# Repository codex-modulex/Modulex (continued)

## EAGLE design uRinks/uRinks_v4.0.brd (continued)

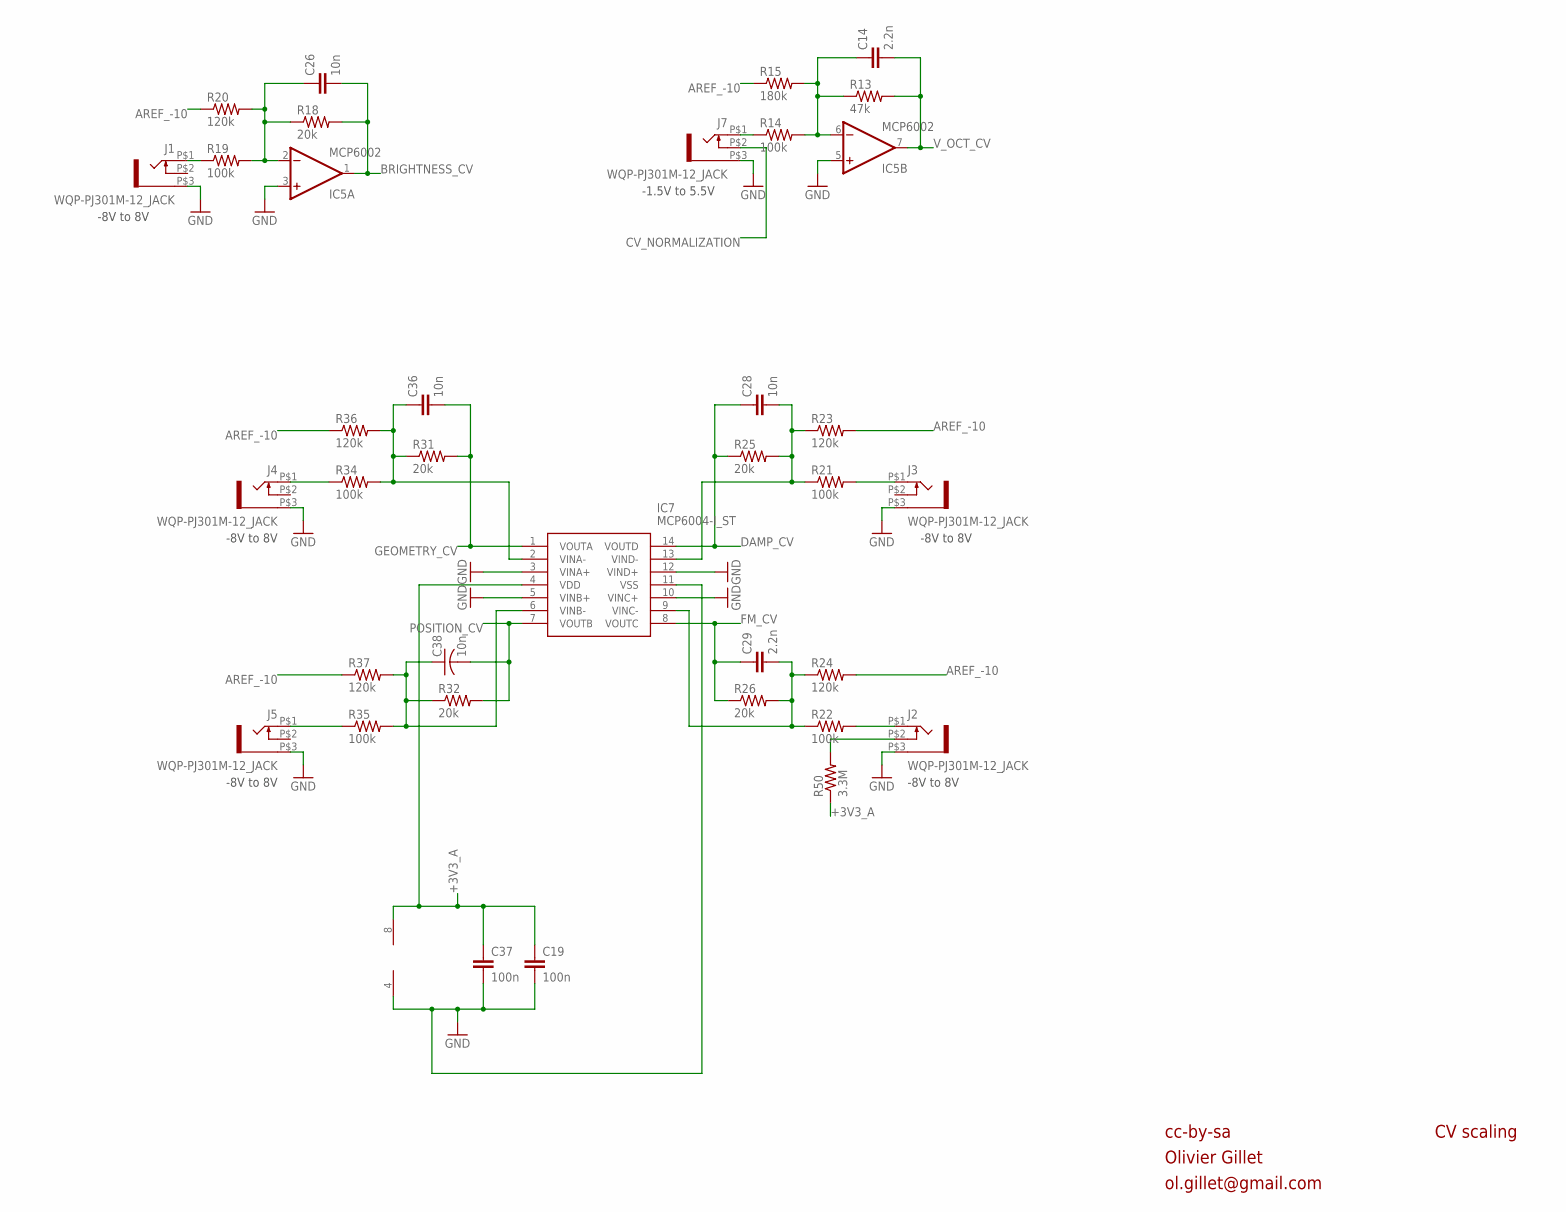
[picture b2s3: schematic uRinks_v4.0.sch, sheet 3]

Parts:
C14, C29: 2.2n; PARTS_AMAN_RESISTOR_0603
C19, C37: 100n; PARTS_AMAN_RESISTOR_0603
C26, C28, C36: 10n; PARTS_AMAN_RESISTOR_0603
C38: 10n; C0603
IC5: MCP6002; SO08
IC7: MCP6004-I_ST; SOP65P640X120-14N
J1, J2, J3, J4, J5, J7: WQP-PJ301M-12_JACK
R13: 47k; PARTS_AMAN_RESISTOR_0603
R14, R19, R21, R22, R34, R35: 100k; PARTS_AMAN_RESISTOR_0603
R15: 180k; PARTS_AMAN_RESISTOR_0603
R18, R25, R26, R31, R32: 20k; PARTS_AMAN_RESISTOR_0603
R20, R23, R24, R36, R37: 120k; PARTS_AMAN_RESISTOR_0603
R50: 3.3M; PARTS_AMAN_RESISTOR_0603

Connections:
+3V3_A: C19.1, C37.1, IC5.8 (V+), IC7.4 (VDD), R50.1; also elsewhere on the board
AREF_-10: R15.1, R20.1, R23.2, R24.2, R36.1, R37.1; also elsewhere on the board
BRIGHTNESS_CV: C26.2, IC5.1 (OUT), R18.2; also elsewhere on the board
CV_NORMALIZATION: J7.P$2 (3); also elsewhere on the board
DAMP_CV: C28.1, IC7.14 (VOUTD), R25.1; also elsewhere on the board
FM_CV: C29.1, IC7.8 (VOUTC), R26.1; also elsewhere on the board
GEOMETRY_CV: C36.2, IC7.1 (VOUTA), R31.2; also elsewhere on the board
GND: C19.2, C37.2, IC5.3 (+IN), IC5.4 (V-), IC5.5 (+IN), IC7.3 (VINA+), IC7.5 (VINB+), IC7.10 (VINC+), IC7.11 (VSS), IC7.12 (VIND+), J1.P$3 (1), J2.P$3 (1), J3.P$3 (1), J4.P$3 (1), J5.P$3 (1), J7.P$3 (1); also elsewhere on the board
unnamed: J1.P$1 (2), R19.1
unnamed: C26.1, IC5.2 (-IN), R18.1, R19.2, R20.2
unnamed: J7.P$1 (2), R14.1
unnamed: J3.P$1 (2), R21.2
unnamed: J2.P$1 (2), R22.2
unnamed: C29.2, IC7.9 (VINC-), R22.1, R24.1, R26.2
unnamed: C14.1, IC5.6 (-IN), R13.1, R14.2, R15.2
unnamed: C28.2, IC7.13 (VIND-), R21.1, R23.1, R25.2
unnamed: J4.P$1 (2), R34.1
unnamed: C36.1, IC7.2 (VINA-), R31.1, R34.2, R36.2
unnamed: J5.P$1 (2), R35.1
unnamed: C38.1, IC7.6 (VINB-), R32.1, R35.2, R37.2
unnamed: J2.P$2 (3), R50.2
POSITION_CV: C38.2, IC7.7 (VOUTB), R32.2; also elsewhere on the board
V_OCT_CV: C14.2, IC5.7 (OUT), R13.2; also elsewhere on the board

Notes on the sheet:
cc-by-sa
Olivier Gillet
ol.gillet@gmail.com
CV scaling
-8V to 8V
-1.5V to 5.5V

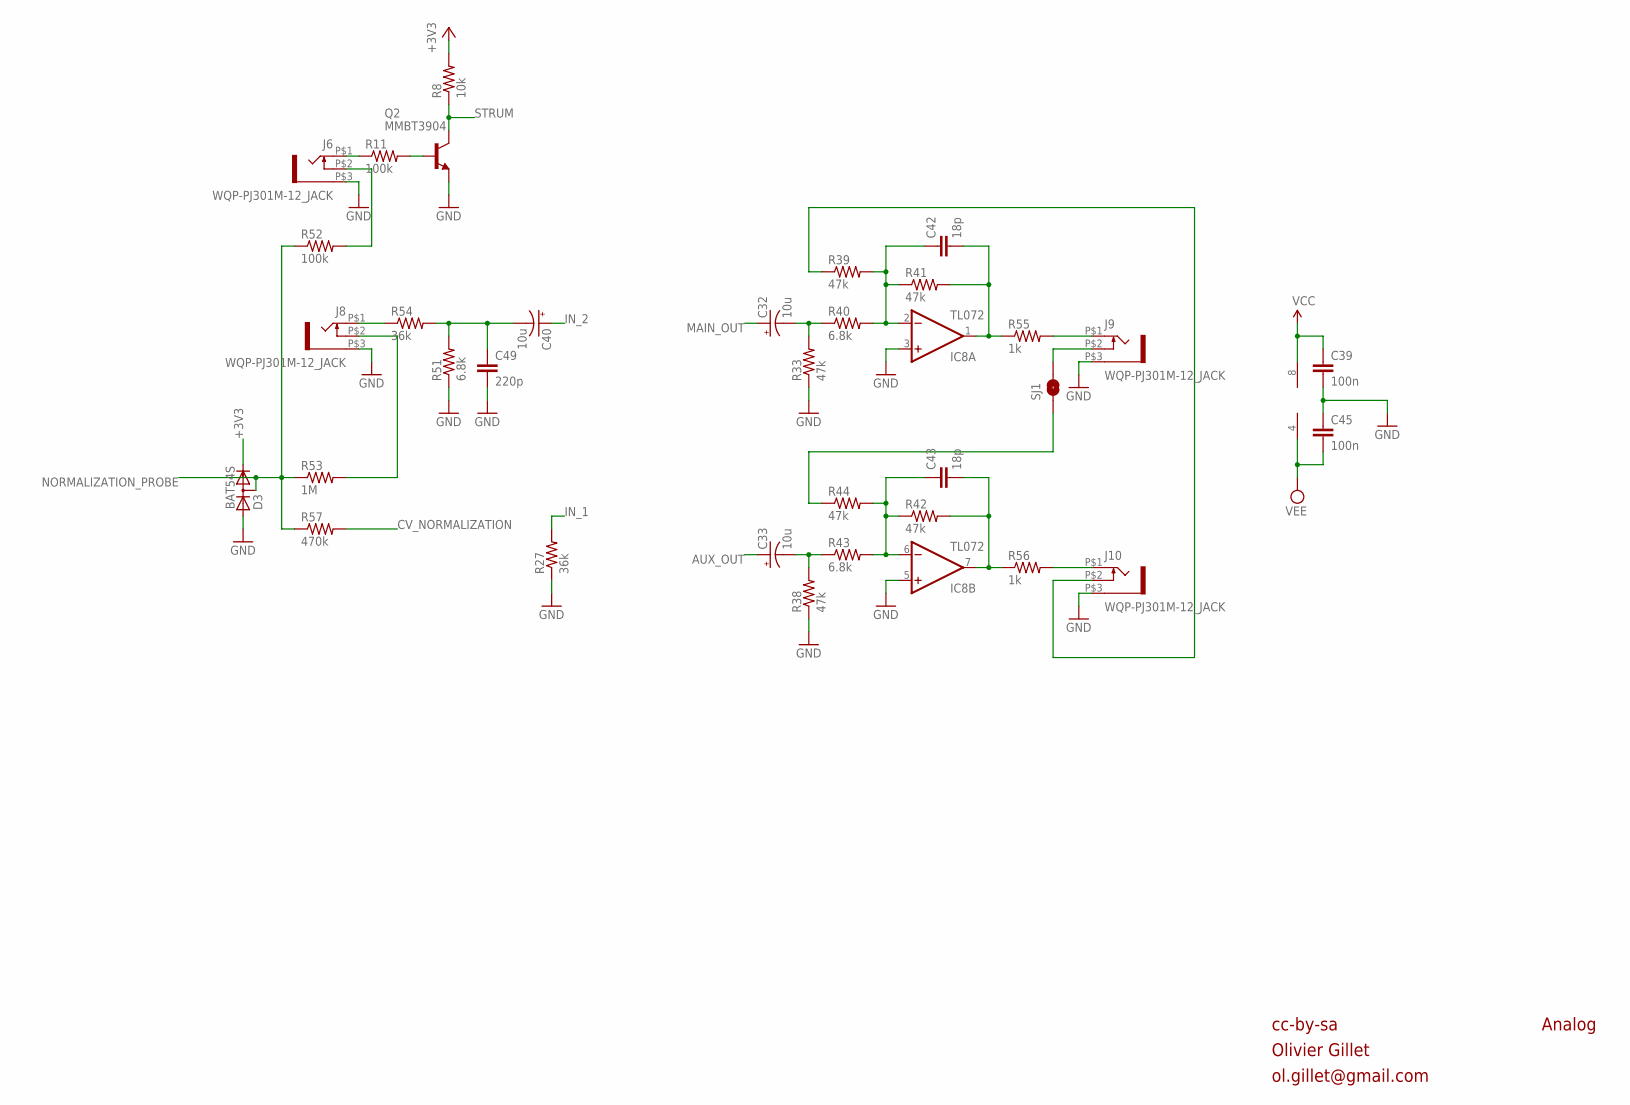
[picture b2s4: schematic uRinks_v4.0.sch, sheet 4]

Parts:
C32, C33, C40: 10u; PANASONIC_A
C39, C45: 100n; PARTS_AMAN_RESISTOR_0603
C42, C43: 18p; PARTS_AMAN_RESISTOR_0603
C49: 220p; PARTS_AMAN_RESISTOR_0603
D3: BAT54S; SOT23
IC8: TL072; SO08
J6, J8, J9, J10: WQP-PJ301M-12_JACK
Q2: MMBT3904; SOT23-BEC
R8: 10k; PARTS_AMAN_RESISTOR_0603
R11: 100k; PARTS_AMAN_RESISTOR_0603
R27, R54: 36k; PARTS_AMAN_RESISTOR_0603
R33, R38, R39, R41, R42, R44: 47k; PARTS_AMAN_RESISTOR_0603
R40, R43, R51: 6.8k; PARTS_AMAN_RESISTOR_0603
R52: 100k; R0603
R53: 1M; PARTS_AMAN_RESISTOR_0603
R55, R56: 1k; PARTS_AMAN_RESISTOR_0603
R57: 470k; PARTS_AMAN_RESISTOR_0603
SJ1: SOLDERJUMPERNC2; SJ_2S-NOTRACE

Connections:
+3V3: D3.2 (C), R8.2; also elsewhere on the board
AUX_OUT: C33.+; also elsewhere on the board
CV_NORMALIZATION: R57.2; also elsewhere on the board
GND: C39.2, C45.1, C49.2, D3.1 (A), IC8.3 (+IN), IC8.5 (+IN), J6.P$3 (1), J8.P$3 (1), J9.P$3 (1), J10.P$3 (1), Q2.E, R27.1, R33.1, R38.1, R51.1; also elsewhere on the board
IN_1: R27.2; also elsewhere on the board
IN_2: C40.+; also elsewhere on the board
MAIN_OUT: C32.+; also elsewhere on the board
unnamed: J6.P$1 (2), R11.1
unnamed: C40.-, C49.1, R51.2, R54.2
unnamed: J6.P$2 (3), R52.2
unnamed: J8.P$1 (2), R54.1
unnamed: C33.-, R38.2, R43.1
unnamed: C43.1, IC8.6 (-IN), R42.1, R43.2, R44.2
unnamed: C43.2, IC8.7 (OUT), R42.2, R56.1
unnamed: J10.P$1 (2), R56.2
unnamed: C32.-, R33.2, R40.1
unnamed: C42.1, IC8.2 (-IN), R39.2, R40.2, R41.1
unnamed: C42.2, IC8.1 (OUT), R41.2, R55.1
unnamed: J9.P$1 (2), R55.2
unnamed: J8.P$2 (3), R53.2
unnamed: J10.P$2 (3), R39.1
unnamed: R44.1, SJ1.1
unnamed: J9.P$2 (3), SJ1.2
unnamed: Q2.B, R11.2
NORMALIZATION_PROBE: D3.3 (AC), R52.1, R53.1, R57.1; also elsewhere on the board
STRUM: Q2.C, R8.1; also elsewhere on the board
VCC: C39.1, IC8.8 (V+); also elsewhere on the board
VEE: C45.2, IC8.4 (V-); also elsewhere on the board

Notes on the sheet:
cc-by-sa
Olivier Gillet
ol.gillet@gmail.com
Analog

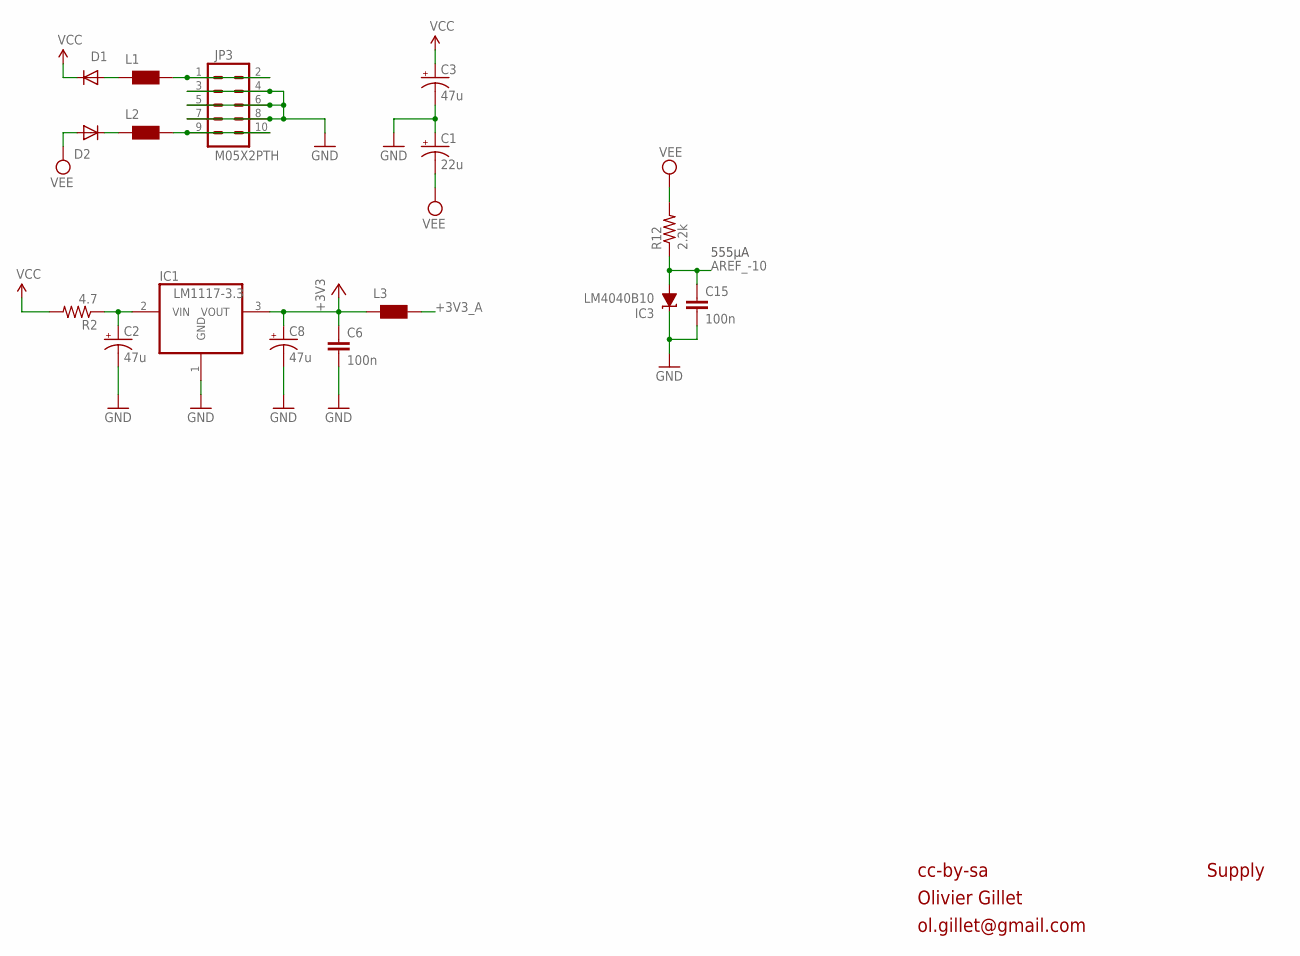
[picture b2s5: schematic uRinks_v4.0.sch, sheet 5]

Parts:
C1: 22u; PANASONIC_C
C2, C3, C8: 47u; PANASONIC_D
C6, C15: 100n; PARTS_AMAN_RESISTOR_0603
D1, D2: 1N5819HW; SOD123
IC1: LM1117-3.3; TO252
IC3: LM4040B10; DBZ_R-PDSO-G3
JP3: M05X2PTH; AVR_ICSP
L1, L2, L3: WE-CBF_0603; 0603
R2: 4.7; R1206
R12: 2.2k; PARTS_AMAN_RESISTOR_0603

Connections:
+3V3: C6.1, C8.+, IC1.3 (VOUT), L3.1; also elsewhere on the board
+3V3_A: L3.2; also elsewhere on the board
AREF_-10: C15.1, IC3.2 (A), R12.1; also elsewhere on the board
GND: C1.+, C2.-, C3.-, C6.2, C8.-, C15.2, IC1.1 (GND), IC3.1 (C), JP3.3, JP3.4, JP3.5, JP3.6, JP3.7, JP3.8; also elsewhere on the board
unnamed: C2.+, IC1.2 (VIN), R2.1
unnamed: D1.A, L1.1
unnamed: D2.C, L2.1
unnamed: JP3.1, JP3.2, L1.2
unnamed: JP3.9, JP3.10, L2.2
VCC: C3.+, D1.C, R2.2; also elsewhere on the board
VEE: C1.-, D2.A, R12.2; also elsewhere on the board

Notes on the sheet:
555µA
cc-by-sa
Olivier Gillet
ol.gillet@gmail.com
Supply

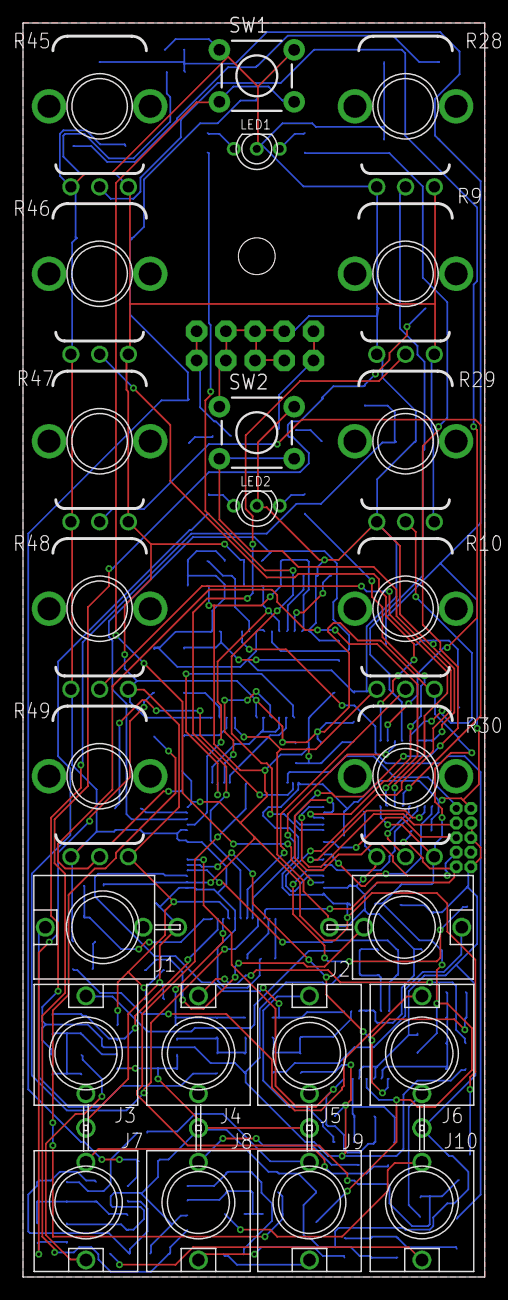
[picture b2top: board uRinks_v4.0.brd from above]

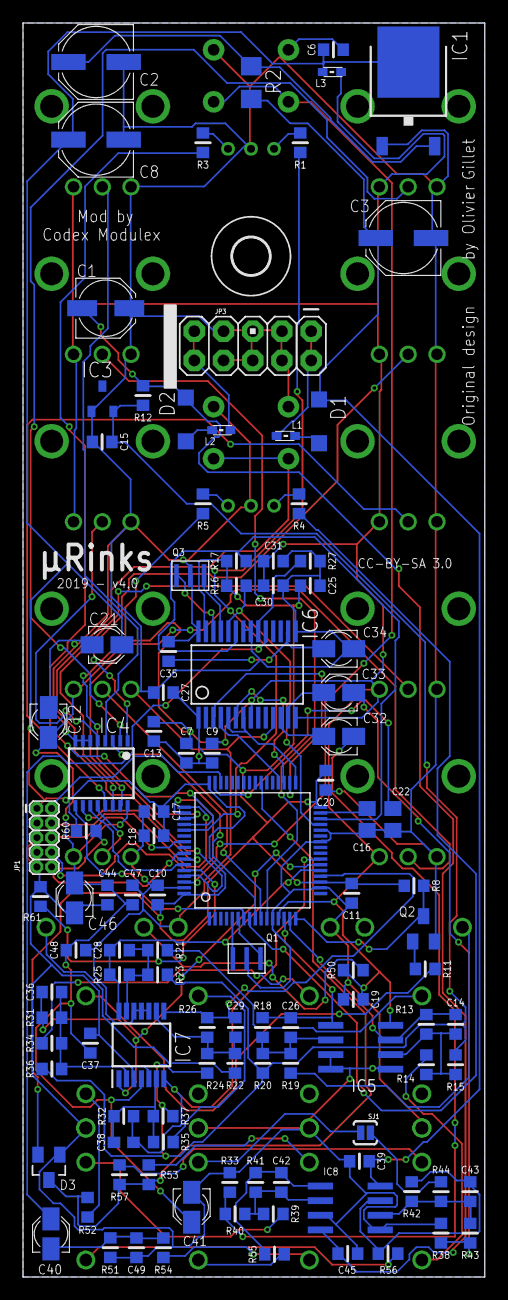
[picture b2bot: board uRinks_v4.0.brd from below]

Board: 2 copper layers, 40.1 x 109.0 mm, 137 parts (113 on the bottom side), 97 nets.

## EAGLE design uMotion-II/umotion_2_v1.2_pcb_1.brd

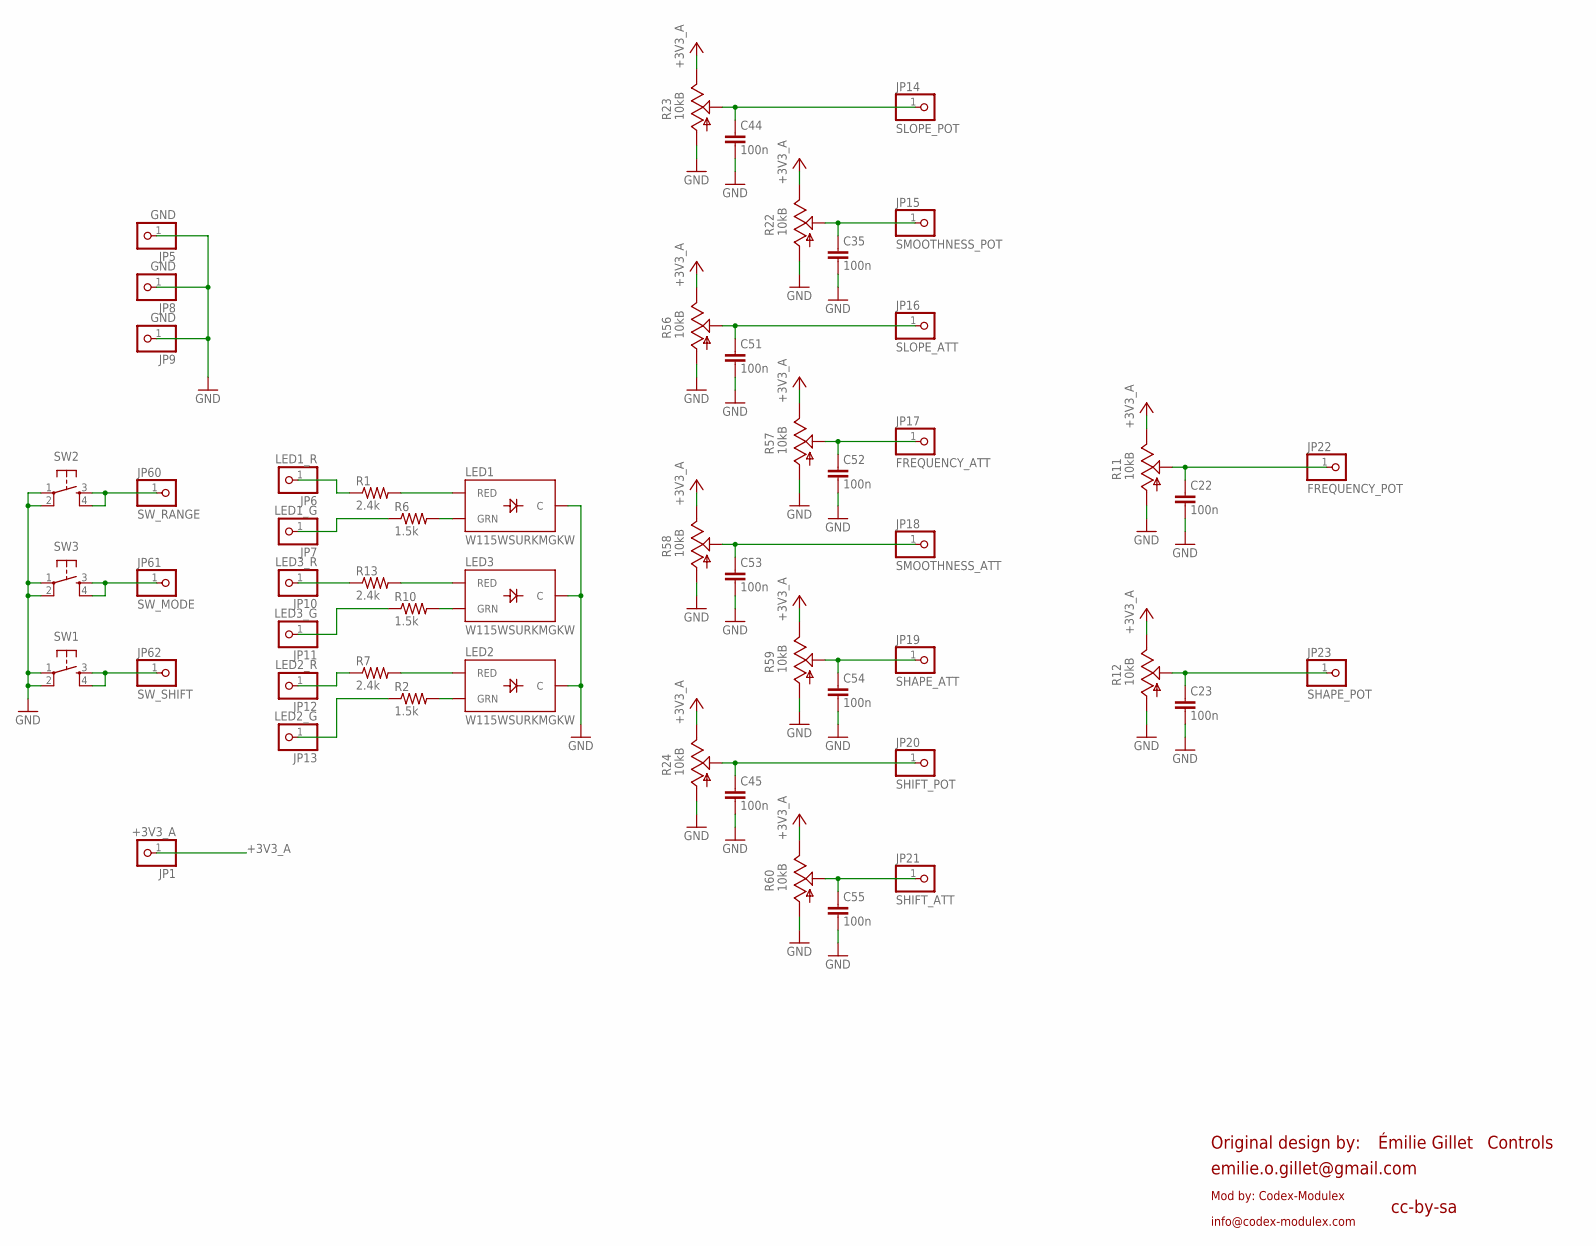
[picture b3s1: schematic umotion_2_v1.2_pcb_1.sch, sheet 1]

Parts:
C22, C23, C35, C44, C45, C51, C52, C53, C54, C55: 100n; PARTS_AMAN_RESISTOR_0603
JP1: +3V3_A; PARTS_AMAN_1X01
JP5, JP8, JP9: GND; PARTS_AMAN_1X01
JP6: LED1_R; PARTS_AMAN_1X01
JP7: LED1_G; PARTS_AMAN_1X01
JP10: LED3_R; PARTS_AMAN_1X01
JP11: LED3_G; PARTS_AMAN_1X01
JP12: LED2_R; PARTS_AMAN_1X01
JP13: LED2_G; PARTS_AMAN_1X01
JP14: SLOPE_POT; PARTS_AMAN_1X01
JP15: SMOOTHNESS_POT; PARTS_AMAN_1X01
JP16: SLOPE_ATT; PARTS_AMAN_1X01
JP17: FREQUENCY_ATT; PARTS_AMAN_1X01
JP18: SMOOTHNESS_ATT; PARTS_AMAN_1X01
JP19: SHAPE_ATT; PARTS_AMAN_1X01
JP20: SHIFT_POT; PARTS_AMAN_1X01
JP21: SHIFT_ATT; PARTS_AMAN_1X01
JP22: FREQUENCY_POT; PARTS_AMAN_1X01
JP23: SHAPE_POT; PARTS_AMAN_1X01
JP60: SW_RANGE; PARTS_AMAN_1X01
JP61: SW_MODE; PARTS_AMAN_1X01
JP62: SW_SHIFT; PARTS_AMAN_1X01
LED1, LED2, LED3: W115WSURKMGKW; LED-BICOLOR-THROUGHHOLE-2.54
R1, R7, R13: 2.4k; PARTS_AMAN_RESISTOR_0603
R2, R6, R10: 1.5k; PARTS_AMAN_RESISTOR_0603
R11, R12, R22, R23, R24, R56, R57, R58, R59, R60: 10kB; ALPS_POT_VERTICAL
SW1, SW2, SW3: TAC_SWITCHPTH; TACTILE-PTH

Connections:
+3V3_A: JP1.1, R11.P$1 (E), R12.P$1 (E), R22.P$1 (E), R23.P$1 (E), R24.P$1 (E), R56.P$1 (E), R57.P$1 (E), R58.P$1 (E), R59.P$1 (E), R60.P$1 (E)
GND: C22.2, C23.2, C35.2, C44.2, C45.2, C51.2, C52.2, C53.2, C54.2, C55.2, JP5.1, JP8.1, JP9.1, LED1.2 (C), LED2.2 (C), LED3.2 (C), R11.P$3 (A), R12.P$3 (A), R22.P$3 (A), R23.P$3 (A), R24.P$3 (A), R56.P$3 (A), R57.P$3 (A), R58.P$3 (A), R59.P$3 (A), R60.P$3 (A), SW1.1, SW1.2, SW2.1, SW2.2, SW3.1, SW3.2; also elsewhere on the board
LED_MODE_G: JP11.1, R10.1
LED_MODE_R: JP10.1, R13.1
LED_RANGE_G: JP7.1, R6.1
LED_RANGE_R: JP6.1, R1.1
LED_SHIFT_G: JP13.1, R2.1
LED_SHIFT_R: JP12.1, R7.1
unnamed: C44.1, JP14.1, R23.P$2 (S)
unnamed: C35.1, JP15.1, R22.P$2 (S)
unnamed: C51.1, JP16.1, R56.P$2 (S)
unnamed: C52.1, JP17.1, R57.P$2 (S)
unnamed: C53.1, JP18.1, R58.P$2 (S)
unnamed: C54.1, JP19.1, R59.P$2 (S)
unnamed: C45.1, JP20.1, R24.P$2 (S)
unnamed: C55.1, JP21.1, R60.P$2 (S)
unnamed: LED1.3 (RED), R1.2
unnamed: LED3.3 (RED), R13.2
unnamed: LED3.1 (GRN), R10.2
unnamed: LED2.3 (RED), R7.2
unnamed: LED1.1 (GRN), R6.2
unnamed: LED2.1 (GRN), R2.2
unnamed: C22.1, JP22.1, R11.P$2 (S)
unnamed: C23.1, JP23.1, R12.P$2 (S)
SW_MODE: JP61.1, SW3.3, SW3.4
SW_RANGE: JP60.1, SW2.3, SW2.4
SW_SHIFT: JP62.1, SW1.3, SW1.4

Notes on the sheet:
cc-by-sa
Controls
Émilie Gillet
emilie.o.gillet@gmail.com
Mod by: Codex-Modulex
Original design by:
info@codex-modulex.com

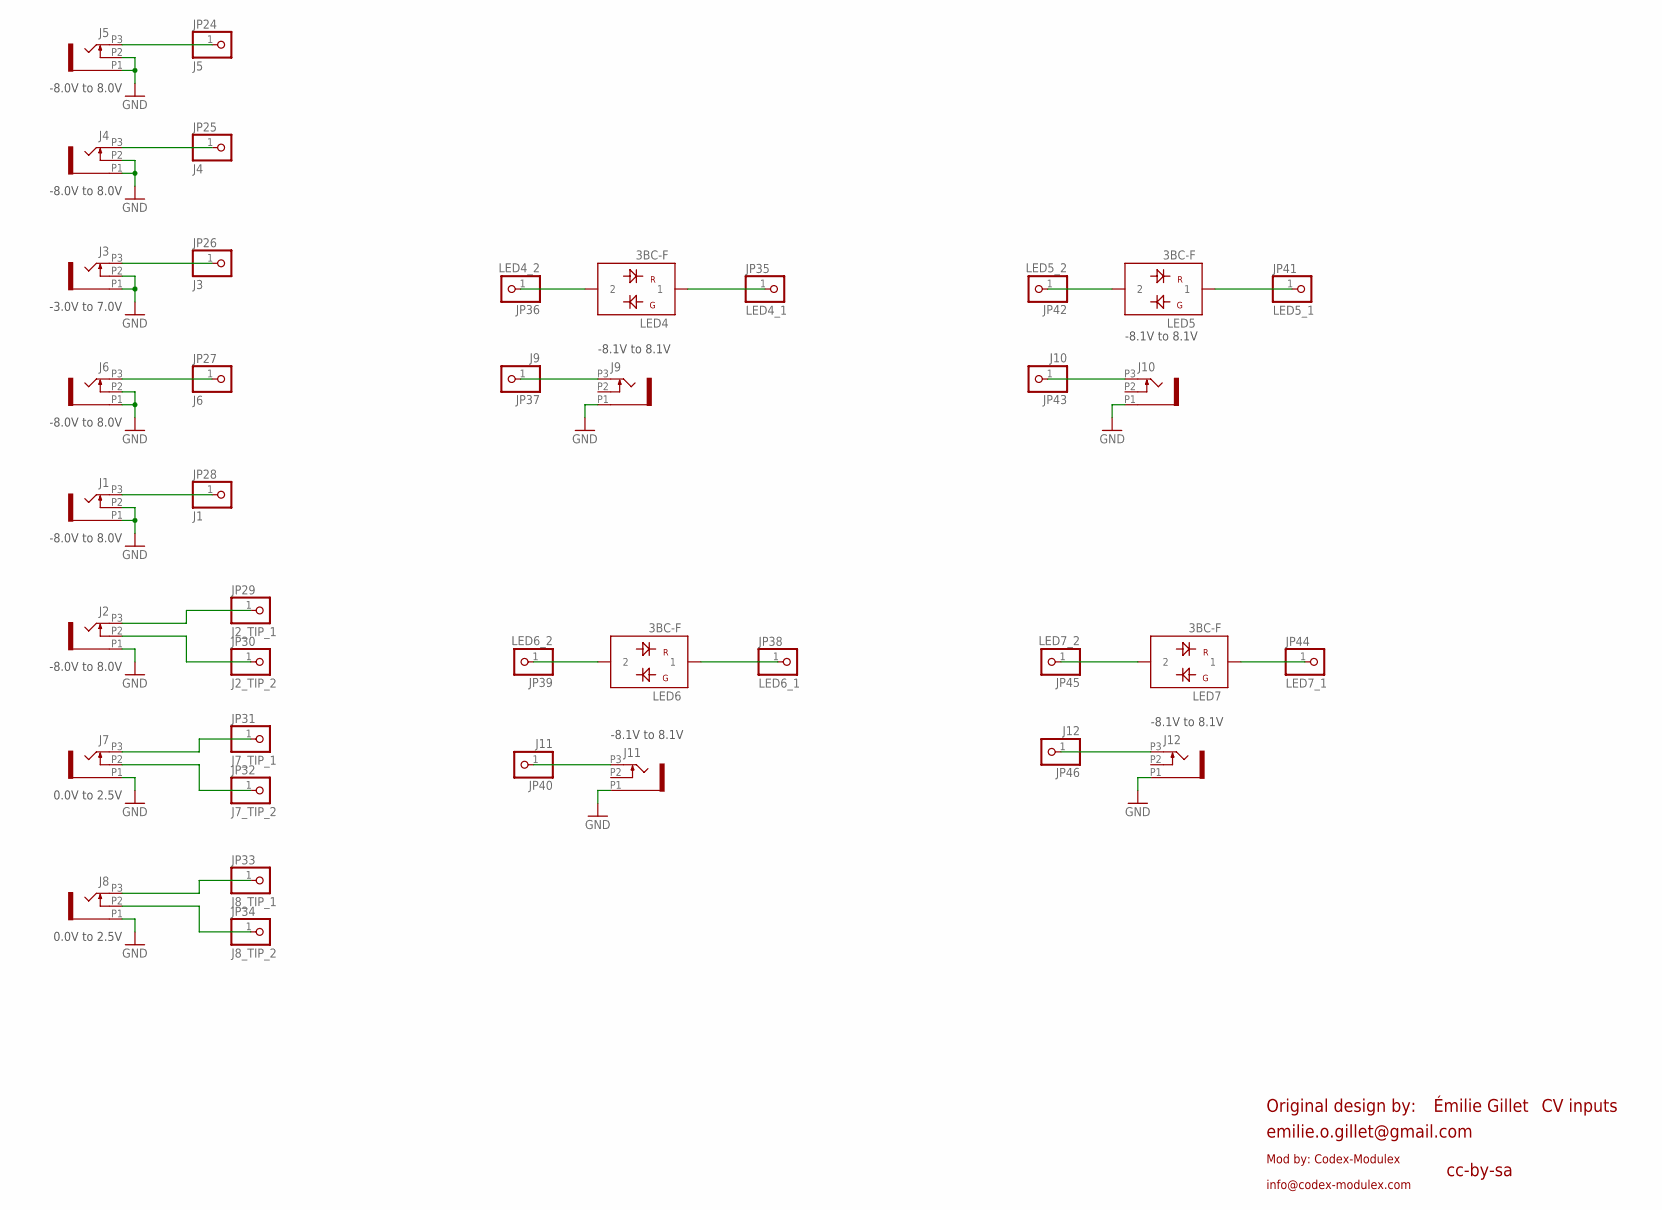
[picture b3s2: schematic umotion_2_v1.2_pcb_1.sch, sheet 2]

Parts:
J1, J2, J3, J4, J5, J6, J7, J8, J9, J10, J11, J12: PJ301_THONKICONN6; WQP_PJ_301M6
JP24: J5; PARTS_AMAN_1X01
JP25: J4; PARTS_AMAN_1X01
JP26: J3; PARTS_AMAN_1X01
JP27: J6; PARTS_AMAN_1X01
JP28: J1; PARTS_AMAN_1X01
JP29: J2_TIP_1; PARTS_AMAN_1X01
JP30: J2_TIP_2; PARTS_AMAN_1X01
JP31: J7_TIP_1; PARTS_AMAN_1X01
JP32: J7_TIP_2; PARTS_AMAN_1X01
JP33: J8_TIP_1; PARTS_AMAN_1X01
JP34: J8_TIP_2; PARTS_AMAN_1X01
JP35: LED4_1; PARTS_AMAN_1X01
JP36: LED4_2; PARTS_AMAN_1X01
JP37: J9; PARTS_AMAN_1X01
JP38: LED6_1; PARTS_AMAN_1X01
JP39: LED6_2; PARTS_AMAN_1X01
JP40: J11; PARTS_AMAN_1X01
JP41: LED5_1; PARTS_AMAN_1X01
JP42: LED5_2; PARTS_AMAN_1X01
JP43: J10; PARTS_AMAN_1X01
JP44: LED7_1; PARTS_AMAN_1X01
JP45: LED7_2; PARTS_AMAN_1X01
JP46: J12; PARTS_AMAN_1X01
LED4, LED5, LED6, LED7: 3BC-F; LED3MM

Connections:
CLOCK_IN: J8.P3 (3), JP33.1
FM_IN: J2.P3 (3), JP29.1
GND: J1.P1 (1), J1.P2 (2), J2.P1 (1), J3.P1 (1), J3.P2 (2), J4.P1 (1), J4.P2 (2), J5.P1 (1), J5.P2 (2), J6.P1 (1), J6.P2 (2), J7.P1 (1), J8.P1 (1), J9.P1 (1), J10.P1 (1), J11.P1 (1), J12.P1 (1); also elsewhere on the board
unnamed: J7.P2 (2), JP32.1
unnamed: J8.P2 (2), JP34.1
unnamed: J9.P3 (3), JP37.1
unnamed: JP36.1, LED4.2
unnamed: JP35.1, LED4.1
unnamed: J11.P3 (3), JP40.1
unnamed: JP39.1, LED6.2
unnamed: JP38.1, LED6.1
unnamed: J10.P3 (3), JP43.1
unnamed: JP42.1, LED5.2
unnamed: JP41.1, LED5.1
unnamed: J2.P2 (2), JP30.1
unnamed: J12.P3 (3), JP46.1
unnamed: JP45.1, LED7.2
unnamed: JP44.1, LED7.1
SHAPE_IN: J5.P3 (3), JP24.1
SHIFT_IN: J6.P3 (3), JP27.1
SLOPE_IN: J1.P3 (3), JP28.1
SMOOTHNESS_IN: J4.P3 (3), JP25.1
TRIG_IN: J7.P3 (3), JP31.1
V_OCT_IN: J3.P3 (3), JP26.1

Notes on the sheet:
CV inputs
-8.0V to 8.0V
-3.0V to 7.0V
0.0V to 2.5V
-8.1V to 8.1V
cc-by-sa
Émilie Gillet
emilie.o.gillet@gmail.com
Mod by: Codex-Modulex
Original design by:
info@codex-modulex.com

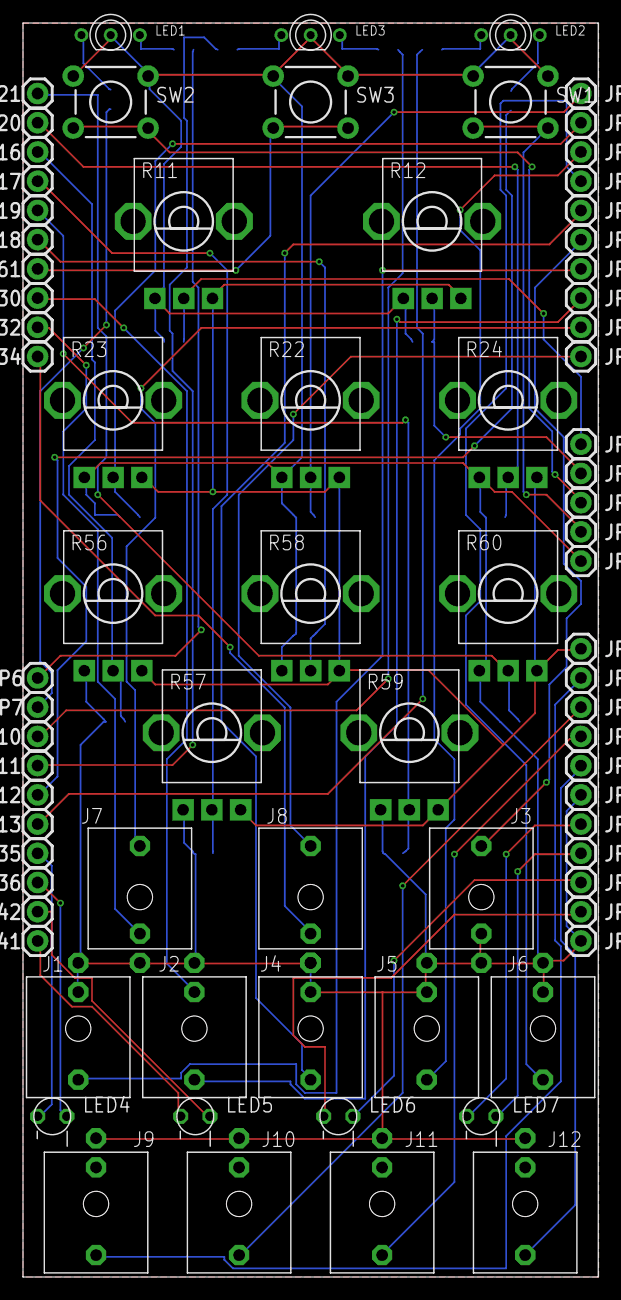
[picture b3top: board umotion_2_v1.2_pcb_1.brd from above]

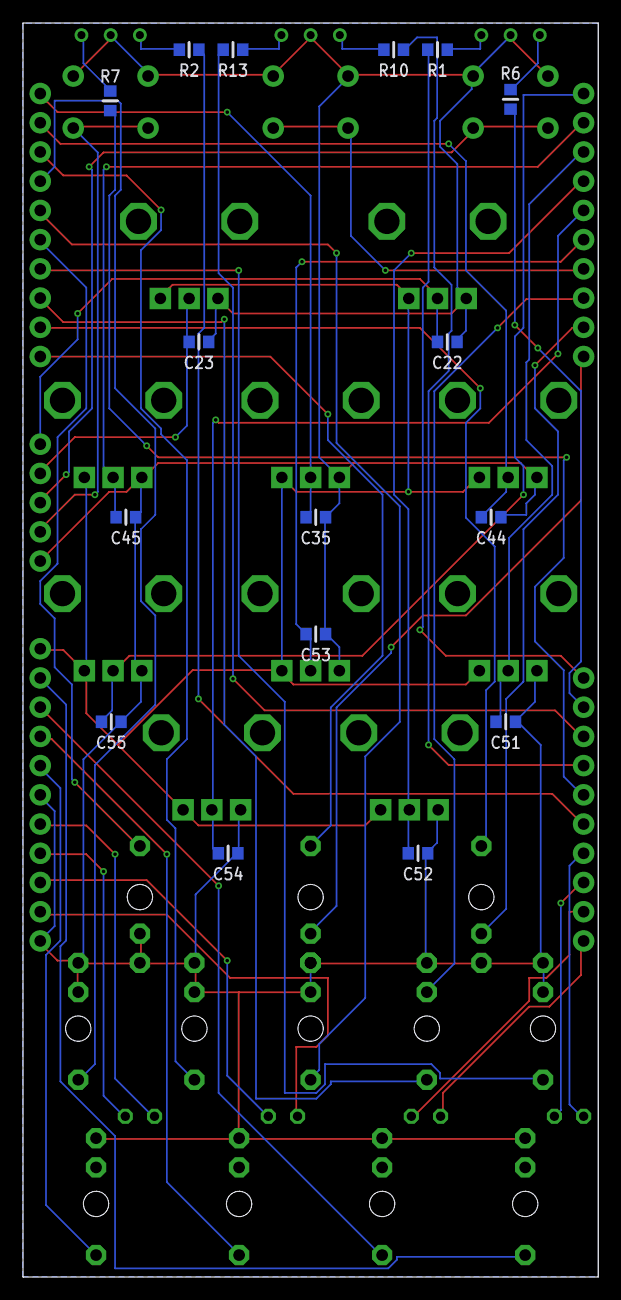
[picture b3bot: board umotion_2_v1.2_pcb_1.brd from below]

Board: 2 copper layers, 50.0 x 109.0 mm, 94 parts (16 on the bottom side), 50 nets.

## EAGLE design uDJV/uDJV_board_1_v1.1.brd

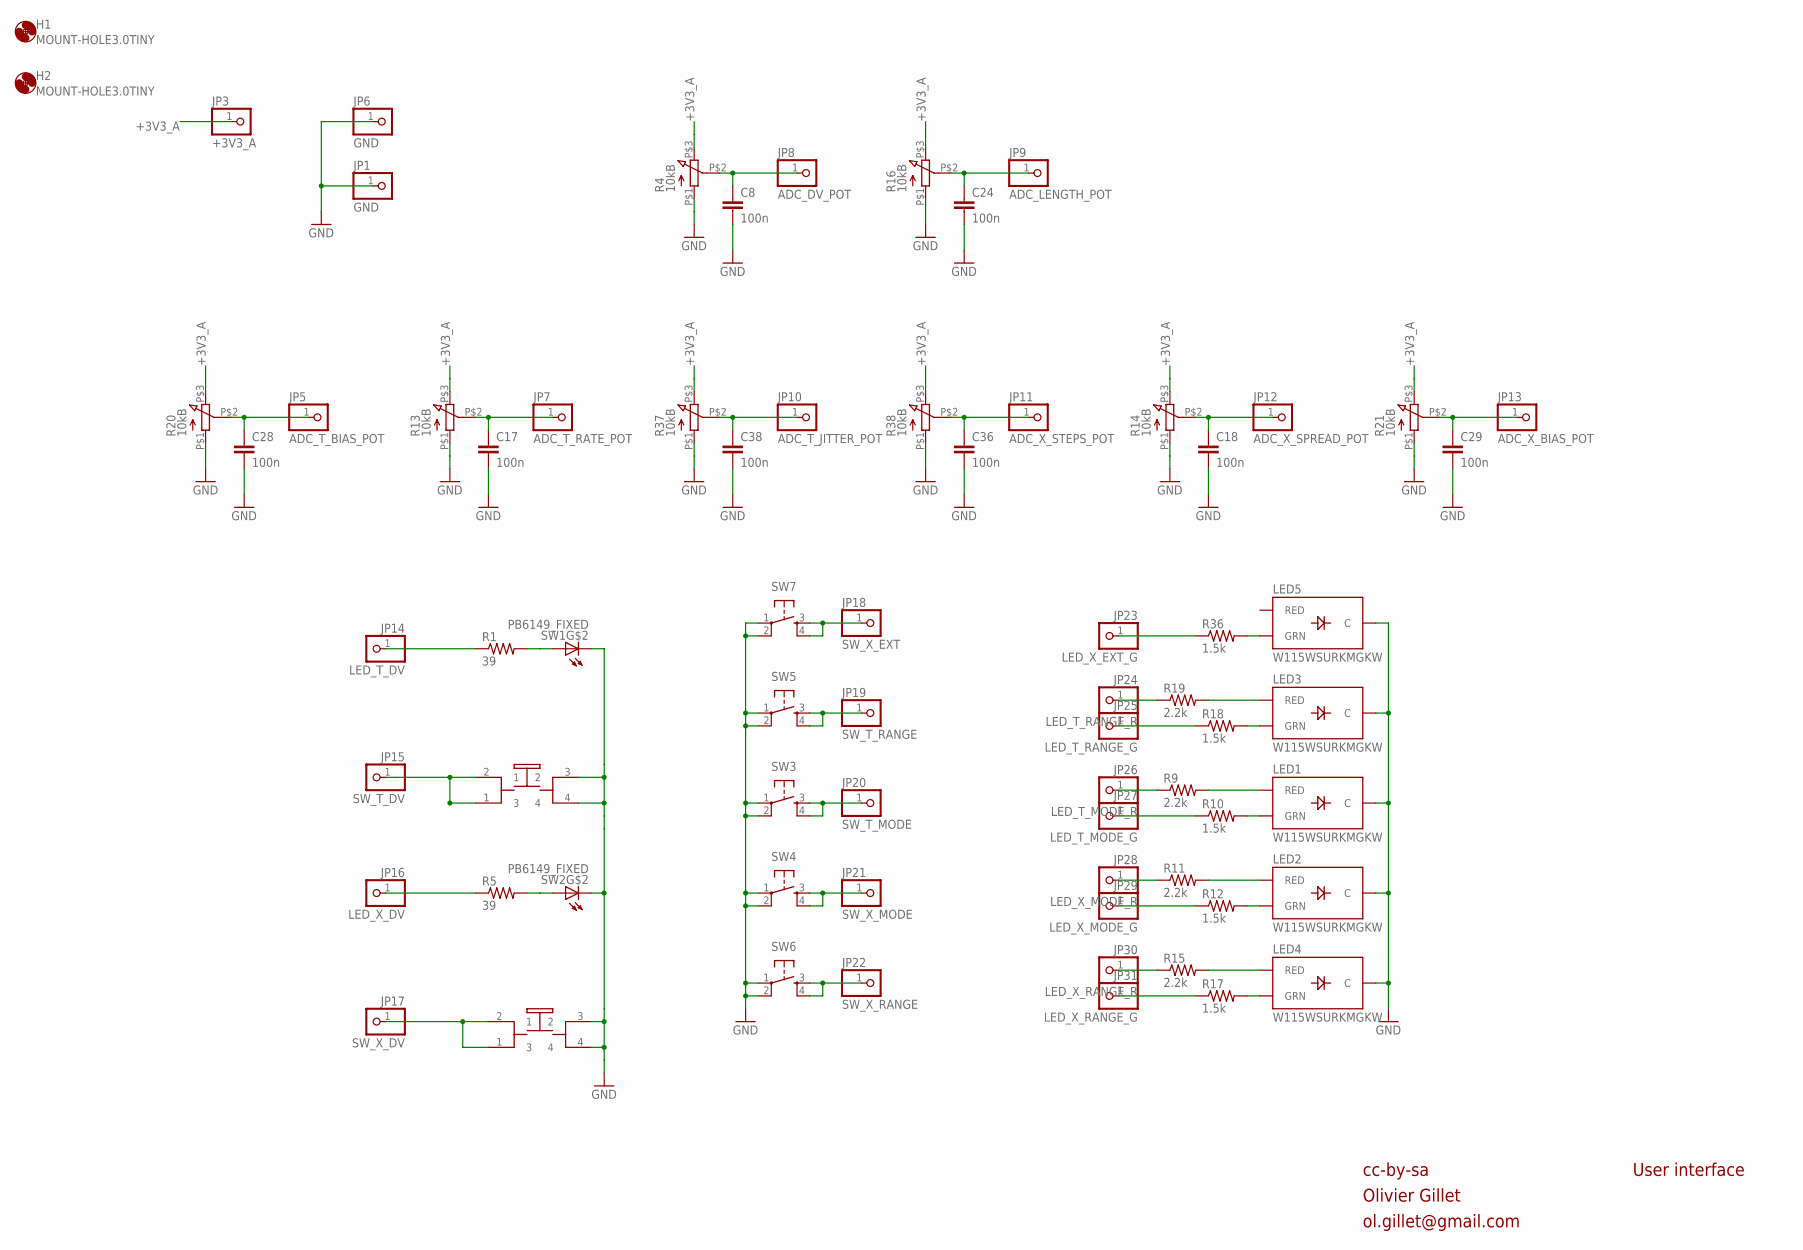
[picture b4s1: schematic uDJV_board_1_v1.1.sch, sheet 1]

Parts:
C8, C17, C18, C24, C28, C29, C36, C38: 100n; PARTS_AMAN_RESISTOR_0603
H1, H2: MOUNT-HOLE3.0TINY; 3,0TINY
JP1, JP6: GND; PARTS_AMAN_1X01
JP3: +3V3_A; PARTS_AMAN_1X01
JP5: ADC_T_BIAS_POT; PARTS_AMAN_1X01
JP7: ADC_T_RATE_POT; PARTS_AMAN_1X01
JP8: ADC_DV_POT; PARTS_AMAN_1X01
JP9: ADC_LENGTH_POT; PARTS_AMAN_1X01
JP10: ADC_T_JITTER_POT; PARTS_AMAN_1X01
JP11: ADC_X_STEPS_POT; PARTS_AMAN_1X01
JP12: ADC_X_SPREAD_POT; PARTS_AMAN_1X01
JP13: ADC_X_BIAS_POT; PARTS_AMAN_1X01
JP14: LED_T_DV; PARTS_AMAN_1X01
JP15: SW_T_DV; PARTS_AMAN_1X01
JP16: LED_X_DV; PARTS_AMAN_1X01
JP17: SW_X_DV; PARTS_AMAN_1X01
JP18: SW_X_EXT; PARTS_AMAN_1X01
JP19: SW_T_RANGE; PARTS_AMAN_1X01
JP20: SW_T_MODE; PARTS_AMAN_1X01
JP21: SW_X_MODE; PARTS_AMAN_1X01
JP22: SW_X_RANGE; PARTS_AMAN_1X01
JP23: LED_X_EXT_G; PARTS_AMAN_1X01
JP24: LED_T_RANGE_R; PARTS_AMAN_1X01
JP25: LED_T_RANGE_G; PARTS_AMAN_1X01
JP26: LED_T_MODE_R; PARTS_AMAN_1X01
JP27: LED_T_MODE_G; PARTS_AMAN_1X01
JP28: LED_X_MODE_R; PARTS_AMAN_1X01
JP29: LED_X_MODE_G; PARTS_AMAN_1X01
JP30: LED_X_RANGE_R; PARTS_AMAN_1X01
JP31: LED_X_RANGE_G; PARTS_AMAN_1X01
LED1, LED2, LED3, LED4, LED5: W115WSURKMGKW; LED-BICOLOR-THROUGHHOLE-2.54
R1, R5: 39; PARTS_AMAN_RESISTOR_0603
R4, R13, R14, R16, R20, R21, R37, R38: 10kB; Q-POT2
R9, R11, R15, R19: 2.2k; PARTS_AMAN_RESISTOR_0603
R10, R12, R17, R18, R36: 1.5k; PARTS_AMAN_RESISTOR_0603
SW1, SW2: PB6149_FIXED; PB6149L
SW3, SW4, SW5, SW6, SW7: TAC_SWITCHPTH; TACTILE-PTH

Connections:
+3V3_A: JP3.1, R4.P$3 (3), R13.P$3 (3), R14.P$3 (3), R16.P$3 (3), R20.P$3 (3), R21.P$3 (3), R37.P$3 (3), R38.P$3 (3)
ADC_DV_POT: C8.1, JP8.1, R4.P$2 (2)
ADC_LENGTH_POT: C24.1, JP9.1, R16.P$2 (2)
ADC_T_BIAS_POT: C28.1, JP5.1, R20.P$2 (2)
ADC_T_JITTER_POT: C38.1, JP10.1, R37.P$2 (2)
ADC_T_RATE_POT: C17.1, JP7.1, R13.P$2 (2)
ADC_X_BIAS_POT: C29.1, JP13.1, R21.P$2 (2)
ADC_X_SPREAD_POT: C18.1, JP12.1, R14.P$2 (2)
ADC_X_STEPS_POT: C36.1, JP11.1, R38.P$2 (2)
GND: C8.2, C17.2, C18.2, C24.2, C28.2, C29.2, C36.2, C38.2, JP1.1, JP6.1, LED1.2 (C), LED2.2 (C), LED3.2 (C), LED4.2 (C), LED5.2 (C), R4.P$1 (1), R13.P$1 (1), R14.P$1 (1), R16.P$1 (1), R20.P$1 (1), R21.P$1 (1), R37.P$1 (1), R38.P$1 (1), SW1.3 (2), SW1.4, SW1.K (C), SW2.3 (2), SW2.4, SW2.K (C), SW3.1, SW3.2, SW4.1, SW4.2, SW5.1, SW5.2, SW6.1, SW6.2, SW7.1, SW7.2; also elsewhere on the board
LED_T_DV: JP14.1, R1.1
LED_X_DV: JP16.1, R5.1
unnamed: R1.2, SW1.A
unnamed: R5.2, SW2.A
unnamed: LED3.3 (RED), R19.2
unnamed: LED3.1 (GRN), R18.2
unnamed: LED1.3 (RED), R9.2
unnamed: LED2.3 (RED), R11.2
unnamed: LED2.1 (GRN), R12.2
unnamed: LED4.3 (RED), R15.2
unnamed: LED1.1 (GRN), R10.2
unnamed: LED4.1 (GRN), R17.2
unnamed: LED5.1 (GRN), R36.2
unnamed: JP23.1, R36.1
unnamed: JP24.1, R19.1
unnamed: JP25.1, R18.1
unnamed: JP26.1, R9.1
unnamed: JP27.1, R10.1
unnamed: JP28.1, R11.1
unnamed: JP29.1, R12.1
unnamed: JP30.1, R15.1
unnamed: JP31.1, R17.1
SW_T_DV: JP15.1, SW1.1 (3), SW1.2 (1)
SW_T_MODE: JP20.1, SW3.3, SW3.4
SW_T_RANGE: JP19.1, SW5.3, SW5.4
SW_X_DV: JP17.1, SW2.1 (3), SW2.2 (1)
SW_X_EXT: JP18.1, SW7.3, SW7.4
SW_X_MODE: JP21.1, SW4.3, SW4.4
SW_X_RANGE: JP22.1, SW6.3, SW6.4

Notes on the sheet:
cc-by-sa
Olivier Gillet
ol.gillet@gmail.com
User interface
